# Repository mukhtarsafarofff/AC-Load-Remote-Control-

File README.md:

(ENG)   There are numerous practical uses for infrared (IR) communication, which is a commonly utilised and simple wireless technology. The most common applications that use infrared communication in daily life are TV/video remote controls, motion sensors, infrared thermometers, air conditioning remote controls, and all other applications.The mechanism of regulation of various settings between user and conditioner , is via a remote control , 

(DEU)   Es gibt zahlreiche praktische Einsatzmöglichkeiten für die Infrarot-Kommunikation (IR), eine häufig genutzte und einfache drahtlose Technologie.  Die häufigsten Anwendungen, die Infrarotkommunikation im täglichen Leben nutzen, sind TV-/Video-Fernbedienungen, Bewegungssensoren, Infrarot-Thermometer, Klimaanlagen-Fernbedienungen und alle anderen Anwendungen. Der Mechanismus zur Regulierung verschiedener Einstellungen zwischen Benutzer und Klimaanlage erfolgt über eine Fernbedienung Steuerung, die auf dem Senden von Infrarotsignalen basiert. In dieser Schaltung verwende ich den Sensor TSOP1738.

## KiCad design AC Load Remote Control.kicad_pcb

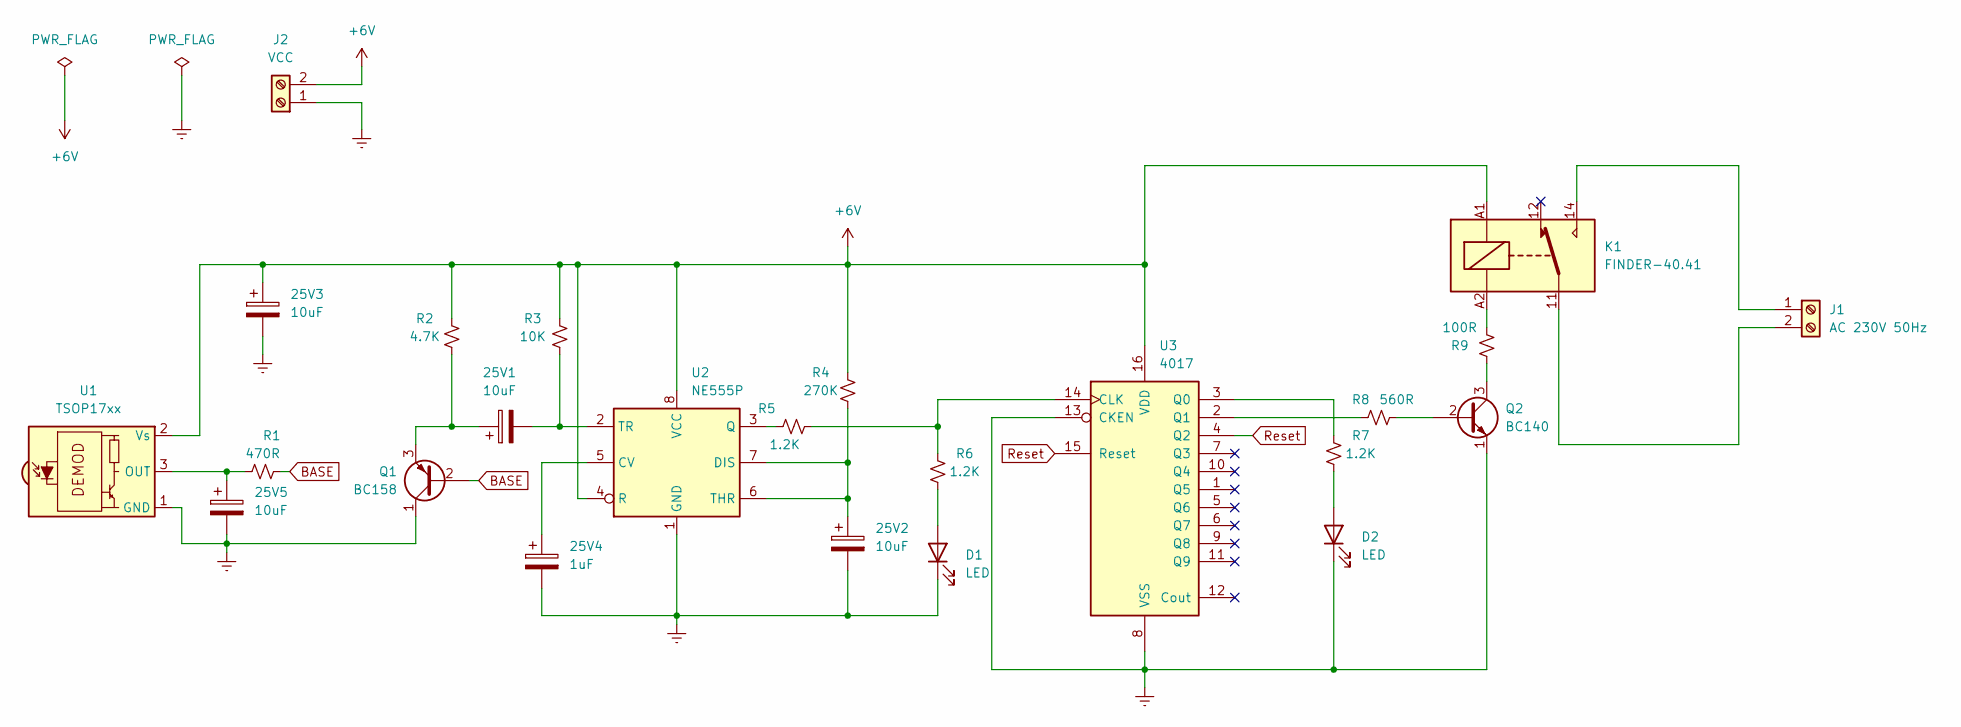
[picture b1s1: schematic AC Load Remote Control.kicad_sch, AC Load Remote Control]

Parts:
25V1, 25V2, 25V3, 25V5: 10uF; CP_Radial_D16.0mm_P7.50mm
25V4: 1uF; CP_Radial_D10.0mm_P7.50mm
D1, D2: LED; LED_D5.0mm
J1: AC 230V 50Hz; TerminalBlock_bornier-2_P5.08mm
J2: VCC; TerminalBlock_bornier-2_P5.08mm
K1: FINDER-40.41; Relay_SPDT_Finder_40.41
Q1: BC158; TO-92_Inline
Q2: BC140; TO-39-3
R1: 470R; R_Axial_DIN0207_L6.3mm_D2.5mm_P15.24mm_Horizontal
R2: 4.7K; R_Axial_DIN0207_L6.3mm_D2.5mm_P15.24mm_Horizontal
R3: 10K; R_Axial_DIN0207_L6.3mm_D2.5mm_P15.24mm_Horizontal
R4: 270K; R_Axial_DIN0207_L6.3mm_D2.5mm_P15.24mm_Horizontal
R5, R6, R7: 1.2K; R_Axial_DIN0207_L6.3mm_D2.5mm_P15.24mm_Horizontal
R8: 560R; R_Axial_DIN0207_L6.3mm_D2.5mm_P15.24mm_Horizontal
R9: 100R; R_Axial_DIN0207_L6.3mm_D2.5mm_P15.24mm_Horizontal
U1: TSOP17xx; Vishay_CAST-3Pin
U2: NE555P; DIP-8_W7.62mm
U3: 4017; DIP-16_W7.62mm

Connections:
+6V: 25V3.1, J2.2, K1.A1, R2.2, R3.2, R4.2, U1.2 (Vs), U2.4 (R), U2.8 (VCC), U3.16 (VDD)
BASE: Q1.2 (B), R1.2
Earth: 25V2.2, 25V3.2, 25V4.2, 25V5.2, D1.1 (K), D2.1 (K), J2.1, Q1.1 (C), Q2.1 (E), U1.1 (GND), U2.1 (GND), U3.8 (VSS), U3.13 (CKEN)
unnamed: D1.2 (A), R6.2
unnamed: D2.2 (A), R7.2
unnamed: J1.1, K1.14
unnamed: J1.2, K1.11
unnamed: K1.A2, R9.2
unnamed: 25V1.1, Q1.3 (E), R2.1
unnamed: Q2.2 (B), R8.2
unnamed: Q2.3 (C), R9.1
unnamed: 25V5.1, R1.1, U1.3 (OUT)
unnamed: 25V4.1, U2.5 (CV)
unnamed: 25V2.1, R4.1, U2.6 (THR), U2.7 (DIS)
unnamed: R5.2, U2.3 (Q)
unnamed: 25V1.2, R3.1, U2.2 (TR)
unnamed: R5.1, R6.1, U3.14 (CLK)
unnamed: R7.1, U3.3 (Q0)
unnamed: R8.1, U3.2 (Q1)
Reset: U3.4 (Q2), U3.15 (Reset)

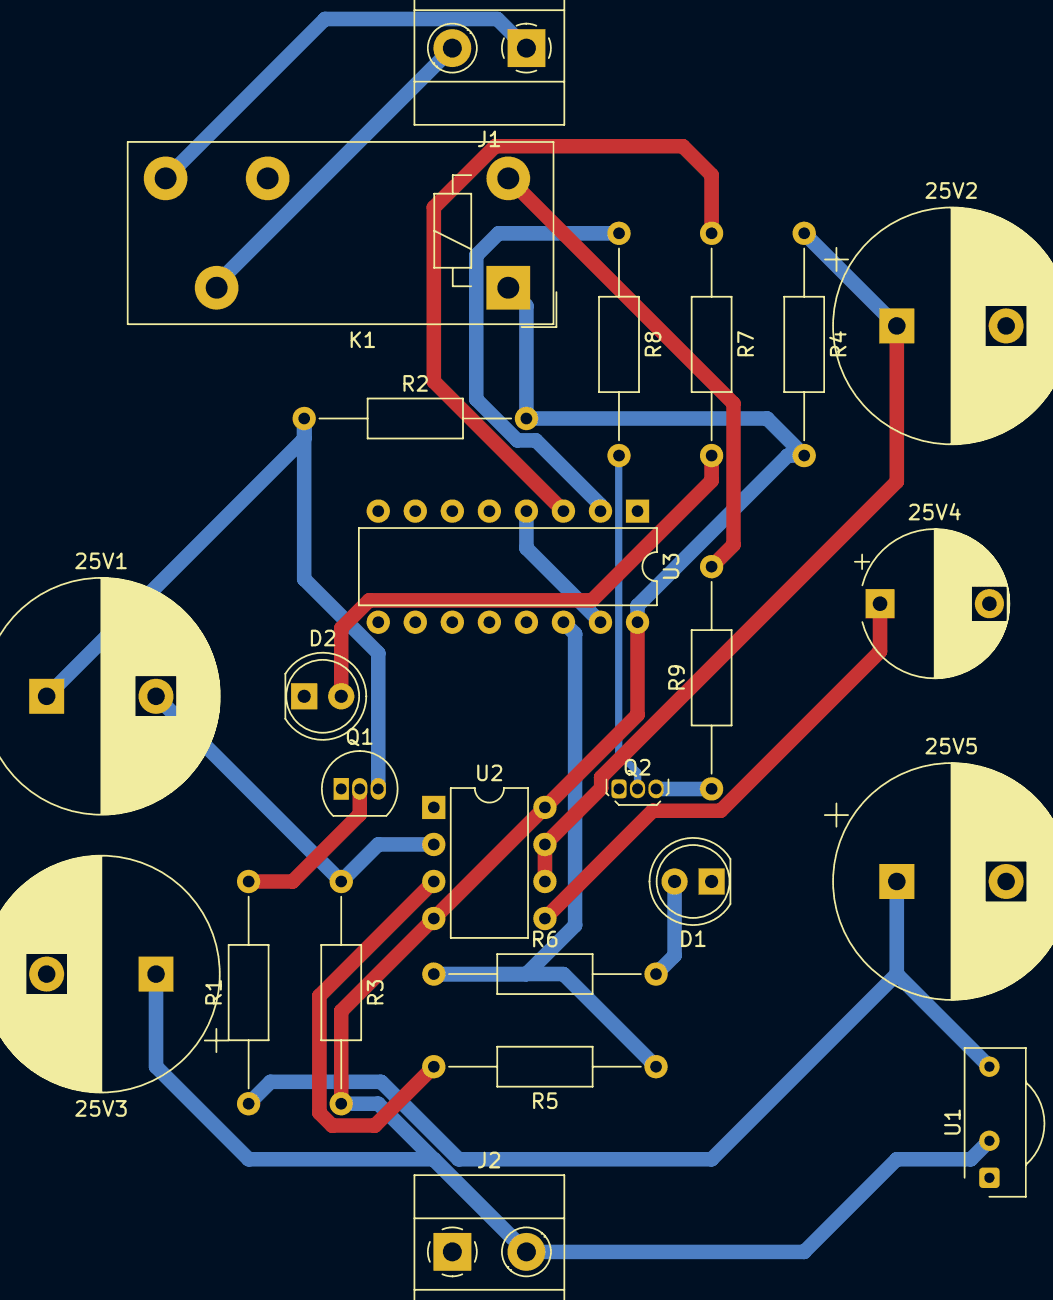
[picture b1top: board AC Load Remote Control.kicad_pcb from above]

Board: 2 copper layers, 24 parts (0 on the bottom side), 20 nets.

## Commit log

2024-04-07 AC Load Remote Control is accomplished
